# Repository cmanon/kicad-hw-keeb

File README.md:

# kicad-hw-keeb
Kicad Hello World Keeb

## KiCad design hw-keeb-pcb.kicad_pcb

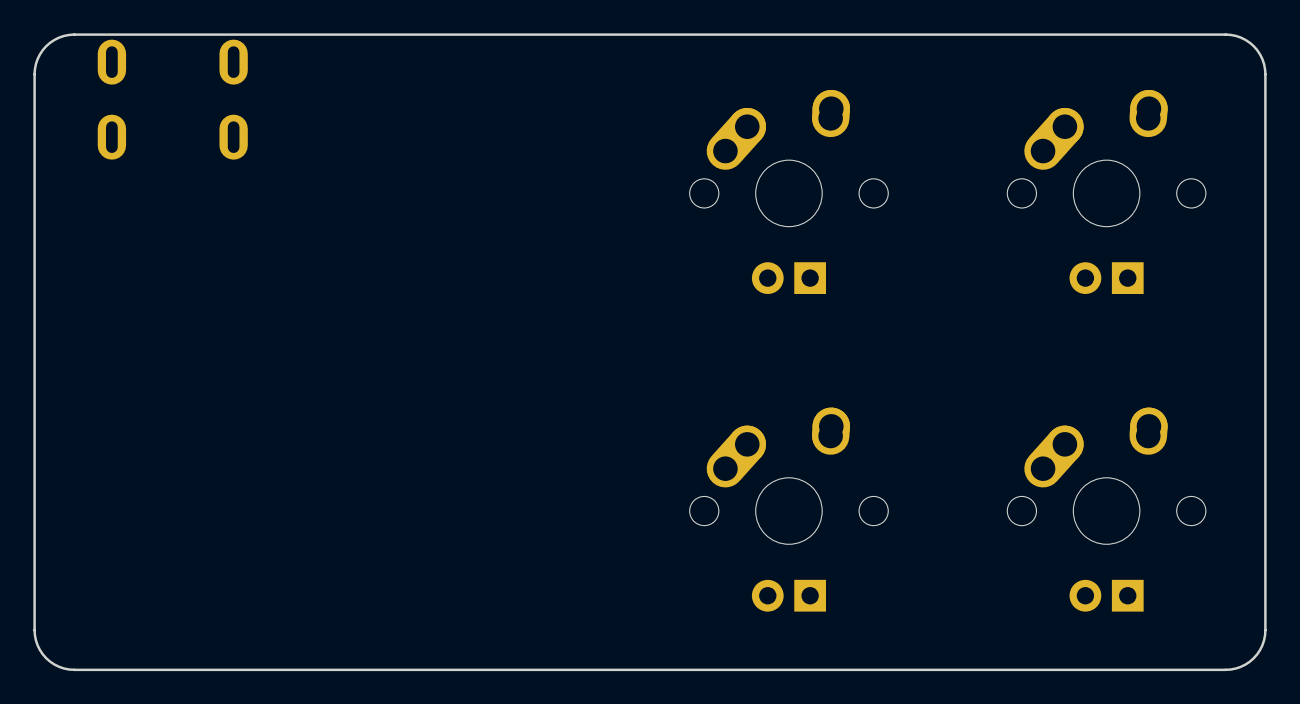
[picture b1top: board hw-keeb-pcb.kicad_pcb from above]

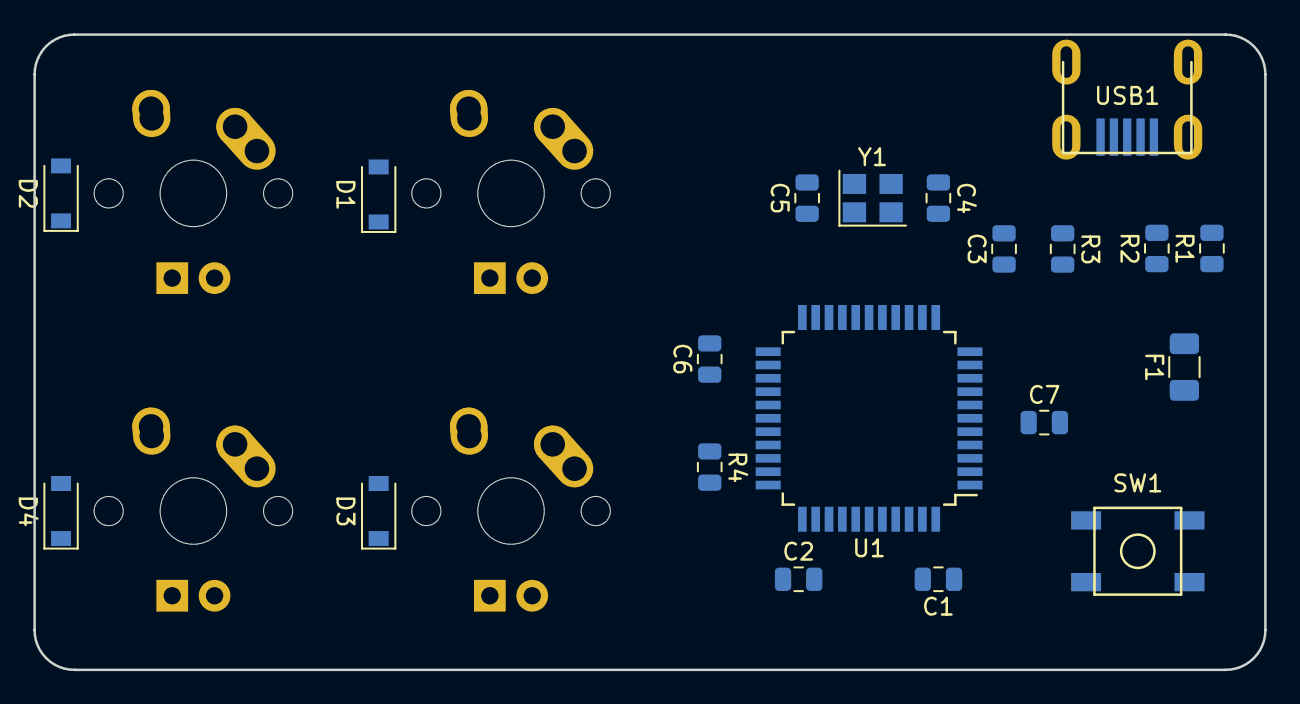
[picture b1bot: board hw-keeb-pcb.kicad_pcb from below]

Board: 2 copper layers, 73.8 x 38.1 mm, 24 parts (20 on the bottom side), 20 nets, no tracks yet.

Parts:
C1, C2, C3, C6: 0.1uF; C_0805_2012Metric
C4, C5: 22pF; C_0805_2012Metric
C7: 1uF; C_0805_2012Metric
D1, D2, D3, D4: D_Small; D_SOD-123
F1: 500mA; Fuse_1206_3216Metric
MX1, MX2, MX3, MX4: MX-1U
R1, R2: 22; R_0805_2012Metric
R3: 10K; R_0805_2012Metric
R4: 10k; R_0805_2012Metric
SW1: SW_Push; SKQG-1155865
U1: ATmega32U4-AU; PQFP-44_10x10mm_P0.8mm
USB1: Molex-0548190589
Y1: 16MHz; Crystal_SMD_3225-4Pin_3.2x2.5mm

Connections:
+5V: C1.1, C2.1, C3.1, C6.1, F1.1, R3.1, U1.2, U1.7, U1.14, U1.24, U1.34, U1.44
COL0: MX1.1, MX2.1
COL1: MX3.1, MX4.1
D+: R2.2, USB1.3
D-: R1.2, USB1.4
GND: C1.2, C2.2, C3.2, C4.2, C5.2, C6.2, C7.2, R4.1, SW1.1, U1.5, U1.15, U1.23, U1.35, U1.43, USB1.1, Y1.2, Y1.4
unnamed: C4.1, U1.17, Y1.1
unnamed: C5.1, U1.16, Y1.3
unnamed: C7.1, U1.6
unnamed: D1.2, MX1.2
unnamed: D2.2, MX2.2
unnamed: D3.2, MX3.2
unnamed: D4.2, MX4.2
unnamed: R1.1, U1.3
unnamed: R2.1, U1.4
unnamed: R3.2, SW1.2, U1.13
unnamed: R4.2, U1.33
ROW0: D1.1, D3.1
ROW1: MX2.4, MX4.4
VCC: F1.2, USB1.5

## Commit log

2019-02-25 Initial commit with submodules.
2019-02-25 Removed subdirectory.
2019-02-25 Added libraries.
2019-02-26 MCU schematic complete.
2019-02-27 Footprints assigned.
2019-03-05 PCB components in place.
2023-03-12 Base matrix schematic added.
2023-03-12 Gitignore update.
2023-03-12 Schematic finish touches.
